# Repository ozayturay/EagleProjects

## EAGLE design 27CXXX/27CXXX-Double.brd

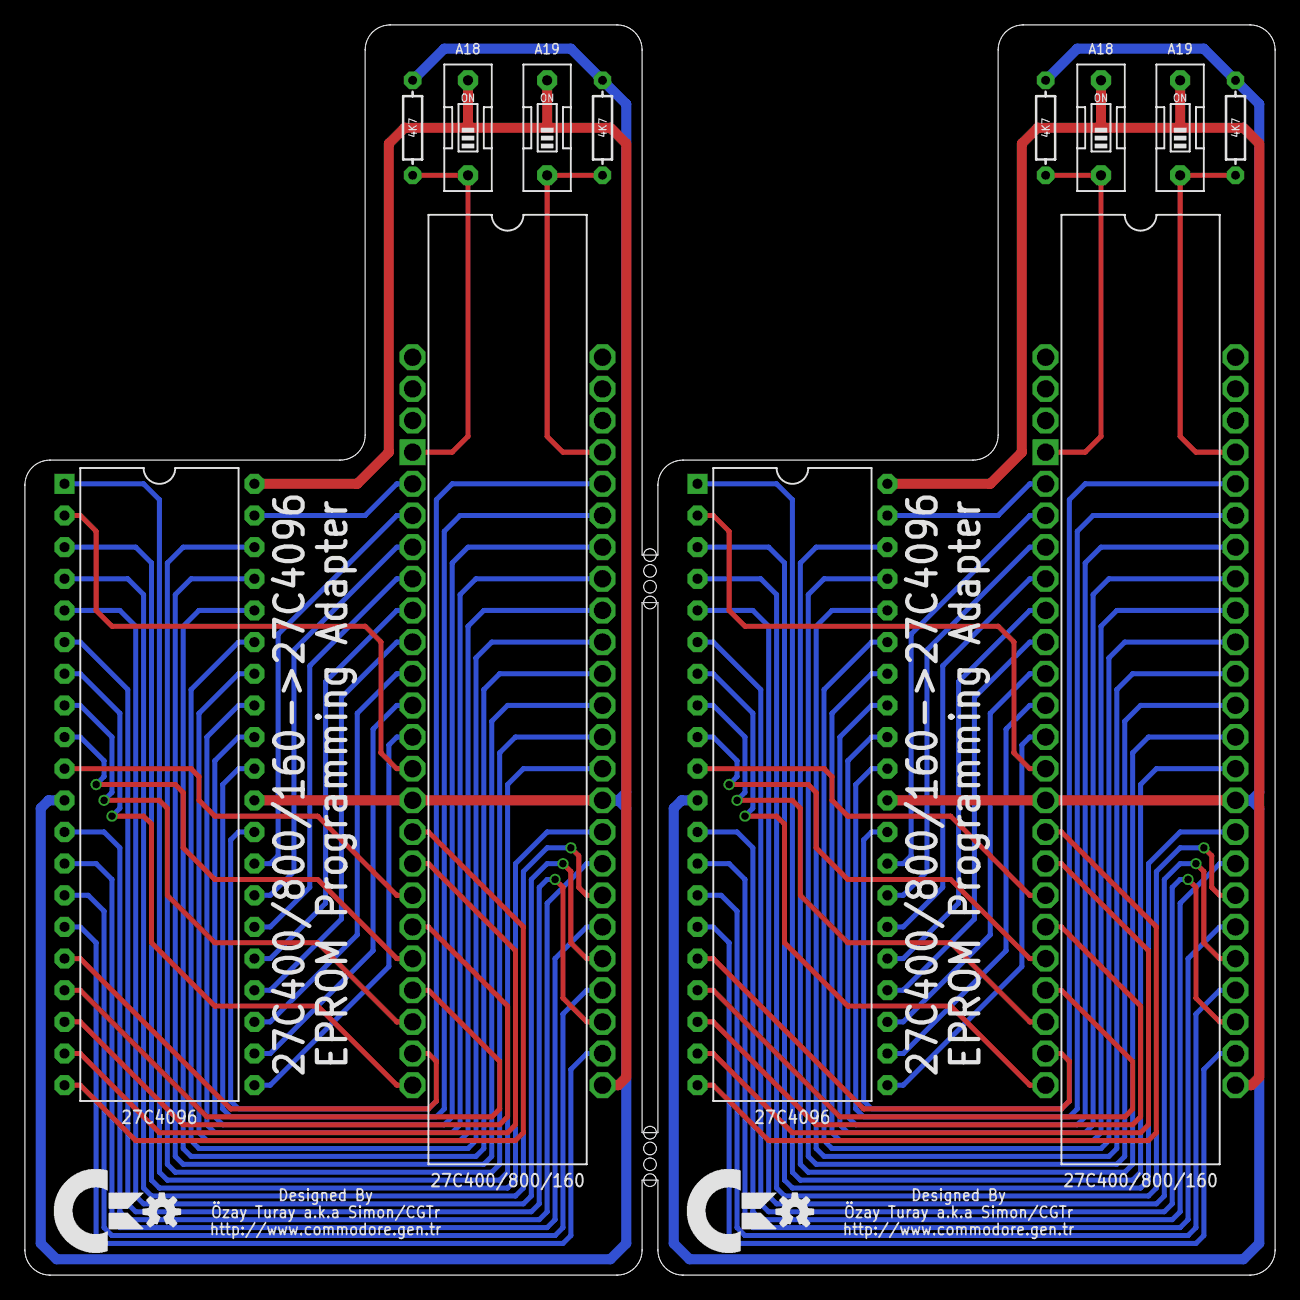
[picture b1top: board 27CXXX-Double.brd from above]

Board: 2 copper layers, 100.3 x 100.3 mm, 14 parts (0 on the bottom side), 82 nets.

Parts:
IC1, IC3: 27C4096; DIP40W
IC2, IC4: 27C400/800/160; ZIF42F
LOGO1, LOGO2: OSHW_LOGO_SMALL
R1, R2, R3, R4: 4K7; RESISTOR_0.3
SW1, SW3: A18; SWITCH_DIP_01
SW2, SW4: A19; SWITCH_DIP_01

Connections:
!CE: IC1.2, IC2.11
!CE1: IC3.2, IC4.11
!OE: IC1.20, IC2.13
!OE1: IC3.20, IC4.13
A0: IC1.21, IC2.10
A1: IC1.22, IC2.9
A2: IC1.23, IC2.8
A3: IC1.24, IC2.7
A4: IC1.25, IC2.6
A5: IC1.26, IC2.5
A6: IC1.27, IC2.4
A7: IC1.28, IC2.3
A8: IC1.29, IC2.41
A9: IC1.31, IC2.40
A10: IC1.32, IC2.39
A11: IC1.33, IC2.38
A12: IC1.34, IC2.37
A13: IC1.35, IC2.36
A14: IC1.36, IC2.35
A15: IC1.37, IC2.34
A16: IC1.38, IC2.33
A17: IC1.39, IC2.2
A18: IC2.1, R1.1, SW1.1
A19: IC2.42, R2.1, SW2.1
A20: IC3.21, IC4.10
A21: IC3.22, IC4.9
A22: IC3.23, IC4.8
A23: IC3.24, IC4.7
A24: IC3.25, IC4.6
A25: IC3.26, IC4.5
A26: IC3.27, IC4.4
A27: IC3.28, IC4.3
A28: IC3.29, IC4.41
A29: IC3.31, IC4.40
A30: IC3.32, IC4.39
A31: IC3.36, IC4.35
A32: IC3.33, IC4.38
A33: IC3.34, IC4.37
A34: IC3.37, IC4.34
A35: IC3.35, IC4.36
A36: IC3.38, IC4.33
A37: IC3.39, IC4.2
A38: IC4.1, R3.1, SW3.1
A39: IC4.42, R4.1, SW4.1
GND: IC1.11, IC1.30, IC2.12, IC2.31, R1.2, R2.2
GND1: IC3.11, IC3.30, IC4.12, IC4.31, R3.2, R4.2
Q0: IC1.19, IC2.14
Q1: IC1.18, IC2.16
Q2: IC1.17, IC2.18
Q3: IC1.16, IC2.20
Q4: IC1.15, IC2.23
Q5: IC1.14, IC2.25
Q6: IC1.13, IC2.27
Q7: IC1.12, IC2.29
Q8: IC1.10, IC2.15
Q9: IC1.9, IC2.17
Q10: IC1.8, IC2.19
Q11: IC1.7, IC2.21
Q12: IC1.6, IC2.24
Q13: IC1.5, IC2.26
Q14: IC1.4, IC2.28
Q15: IC1.3, IC2.30
Q16: IC3.19, IC4.14
Q17: IC3.18, IC4.16
Q18: IC3.17, IC4.18
Q19: IC3.16, IC4.20
Q20: IC3.15, IC4.23
Q21: IC3.14, IC4.25
Q22: IC3.13, IC4.27
Q23: IC3.12, IC4.29
Q24: IC3.10, IC4.15
Q25: IC3.9, IC4.17
Q26: IC3.8, IC4.19
Q27: IC3.7, IC4.21
Q28: IC3.6, IC4.24
Q29: IC3.5, IC4.26
Q30: IC3.4, IC4.28
Q31: IC3.3, IC4.30
VCC: IC1.40, IC2.22, SW1.2, SW2.2
VCC1: IC3.40, IC4.22, SW3.2, SW4.2
VPP: IC1.1, IC2.32
VPP1: IC3.1, IC4.32

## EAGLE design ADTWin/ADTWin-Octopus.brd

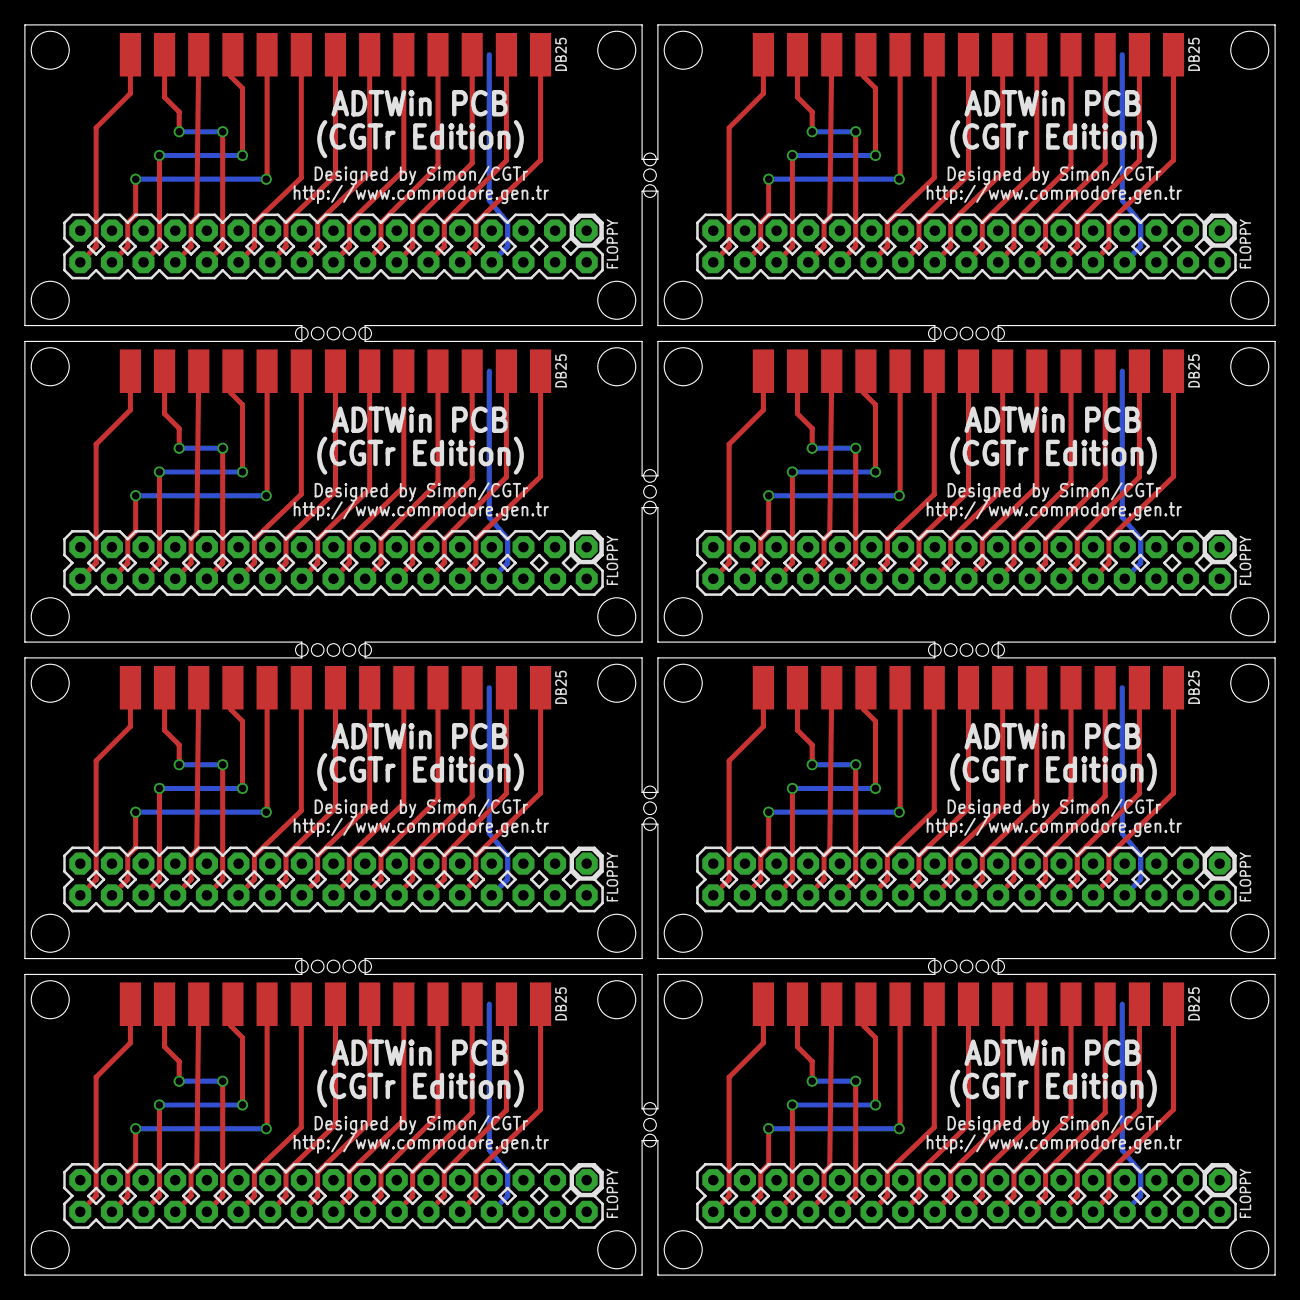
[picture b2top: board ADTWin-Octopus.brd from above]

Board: 2 copper layers, 100.3 x 100.3 mm, 16 parts (0 on the bottom side), 120 nets.

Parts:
JP1, JP2, JP3, JP4, JP5, JP6, JP7, JP8: FLOPPY
X1, X2, X3, X4, X5, X6, X7, X8: DB25; DSUB25-SMD

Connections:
DIR: JP1.18, X1.5
DIR1: JP2.18, X2.5
DIR2: JP3.18, X3.5
DIR3: JP4.18, X4.5
DIR4: JP5.18, X5.5
DIR5: JP6.18, X6.5
DIR6: JP7.18, X7.5
DIR7: JP8.18, X8.5
DRVSA: JP1.14, X1.3
DRVSA1: JP2.14, X2.3
DRVSA2: JP3.14, X3.3
DRVSA3: JP4.14, X4.3
DRVSA4: JP5.14, X5.3
DRVSA5: JP6.14, X6.3
DRVSA6: JP7.14, X7.3
DRVSA7: JP8.14, X8.3
DRVSB: JP1.12, X1.2
DRVSB1: JP2.12, X2.2
DRVSB2: JP3.12, X3.2
DRVSB3: JP4.12, X4.2
DRVSB4: JP5.12, X5.2
DRVSB5: JP6.12, X6.2
DRVSB6: JP7.12, X7.2
DRVSB7: JP8.12, X8.2
DSKCHG: JP1.34, X1.13
DSKCHG1: JP2.34, X2.13
DSKCHG2: JP3.34, X3.13
DSKCHG3: JP4.34, X4.13
DSKCHG4: JP5.34, X5.13
DSKCHG5: JP6.34, X6.13
DSKCHG6: JP7.34, X7.13
DSKCHG7: JP8.34, X8.13
GND: JP1.1, JP1.21, JP1.23, JP1.25, JP1.27, JP1.29, JP1.31, JP1.33, X1.18, X1.19, X1.20, X1.21, X1.22, X1.23, X1.24, X1.25
GND1: JP2.1, JP2.21, JP2.23, JP2.25, JP2.27, JP2.29, JP2.31, JP2.33, X2.18, X2.19, X2.20, X2.21, X2.22, X2.23, X2.24, X2.25
GND2: JP3.1, JP3.21, JP3.23, JP3.25, JP3.27, JP3.29, JP3.31, JP3.33, X3.18, X3.19, X3.20, X3.21, X3.22, X3.23, X3.24, X3.25
GND3: JP4.1, JP4.21, JP4.23, JP4.25, JP4.27, JP4.29, JP4.31, JP4.33, X4.18, X4.19, X4.20, X4.21, X4.22, X4.23, X4.24, X4.25
GND4: JP5.1, JP5.21, JP5.23, JP5.25, JP5.27, JP5.29, JP5.31, JP5.33, X5.18, X5.19, X5.20, X5.21, X5.22, X5.23, X5.24, X5.25
GND5: JP6.1, JP6.21, JP6.23, JP6.25, JP6.27, JP6.29, JP6.31, JP6.33, X6.18, X6.19, X6.20, X6.21, X6.22, X6.23, X6.24, X6.25
GND6: JP7.1, JP7.21, JP7.23, JP7.25, JP7.27, JP7.29, JP7.31, JP7.33, X7.18, X7.19, X7.20, X7.21, X7.22, X7.23, X7.24, X7.25
GND7: JP8.1, JP8.21, JP8.23, JP8.25, JP8.27, JP8.29, JP8.31, JP8.33, X8.18, X8.19, X8.20, X8.21, X8.22, X8.23, X8.24, X8.25
INDEX: JP1.8, X1.15
INDEX1: JP2.8, X2.15
INDEX2: JP3.8, X3.15
INDEX3: JP4.8, X4.15
INDEX4: JP5.8, X5.15
INDEX5: JP6.8, X6.15
INDEX6: JP7.8, X7.15
INDEX7: JP8.8, X8.15
MOTEA: JP1.10, X1.1
MOTEA1: JP2.10, X2.1
MOTEA2: JP3.10, X3.1
MOTEA3: JP4.10, X4.1
MOTEA4: JP5.10, X5.1
MOTEA5: JP6.10, X6.1
MOTEA6: JP7.10, X7.1
MOTEA7: JP8.10, X8.1
MOTEB: JP1.16, X1.4
MOTEB1: JP2.16, X2.4
MOTEB2: JP3.16, X3.4
MOTEB3: JP4.16, X4.4
MOTEB4: JP5.16, X5.4
MOTEB5: JP6.16, X6.4
MOTEB6: JP7.16, X7.4
MOTEB7: JP8.16, X8.4
RDATA: JP1.30, X1.10
RDATA1: JP2.30, X2.10
RDATA2: JP3.30, X3.10
RDATA3: JP4.30, X4.10
RDATA4: JP5.30, X5.10
RDATA5: JP6.30, X6.10
RDATA6: JP7.30, X7.10
RDATA7: JP8.30, X8.10
SIDE1: JP1.32, X1.9
SIDE2: JP2.32, X2.9
SIDE3: JP3.32, X3.9
SIDE4: JP4.32, X4.9
SIDE5: JP5.32, X5.9
SIDE6: JP6.32, X6.9
SIDE7: JP7.32, X7.9
SIDE8: JP8.32, X8.9
STEP: JP1.20, X1.6
STEP1: JP2.20, X2.6
STEP2: JP3.20, X3.6
STEP3: JP4.20, X4.6
STEP4: JP5.20, X5.6
STEP5: JP6.20, X6.6
STEP6: JP7.20, X7.6
STEP7: JP8.20, X8.6
TRK00: JP1.26, X1.12
TRK01: JP2.26, X2.12
TRK02: JP3.26, X3.12
TRK03: JP4.26, X4.12
TRK04: JP5.26, X5.12
TRK05: JP6.26, X6.12
TRK06: JP7.26, X7.12
TRK07: JP8.26, X8.12
WDATA: JP1.22, X1.7
WDATA1: JP2.22, X2.7
WDATA2: JP3.22, X3.7
WDATA3: JP4.22, X4.7
WDATA4: JP5.22, X5.7
WDATA5: JP6.22, X6.7
WDATA6: JP7.22, X7.7
WDATA7: JP8.22, X8.7
WGATE: JP1.24, X1.8
WGATE1: JP2.24, X2.8
WGATE2: JP3.24, X3.8
WGATE3: JP4.24, X4.8
WGATE4: JP5.24, X5.8
WGATE5: JP6.24, X6.8
WGATE6: JP7.24, X7.8
WGATE7: JP8.24, X8.8
WPROT: JP1.28, X1.11
WPROT1: JP2.28, X2.11
WPROT2: JP3.28, X3.11
WPROT3: JP4.28, X4.11
WPROT4: JP5.28, X5.11
WPROT5: JP6.28, X6.11
WPROT6: JP7.28, X7.11
WPROT7: JP8.28, X8.11

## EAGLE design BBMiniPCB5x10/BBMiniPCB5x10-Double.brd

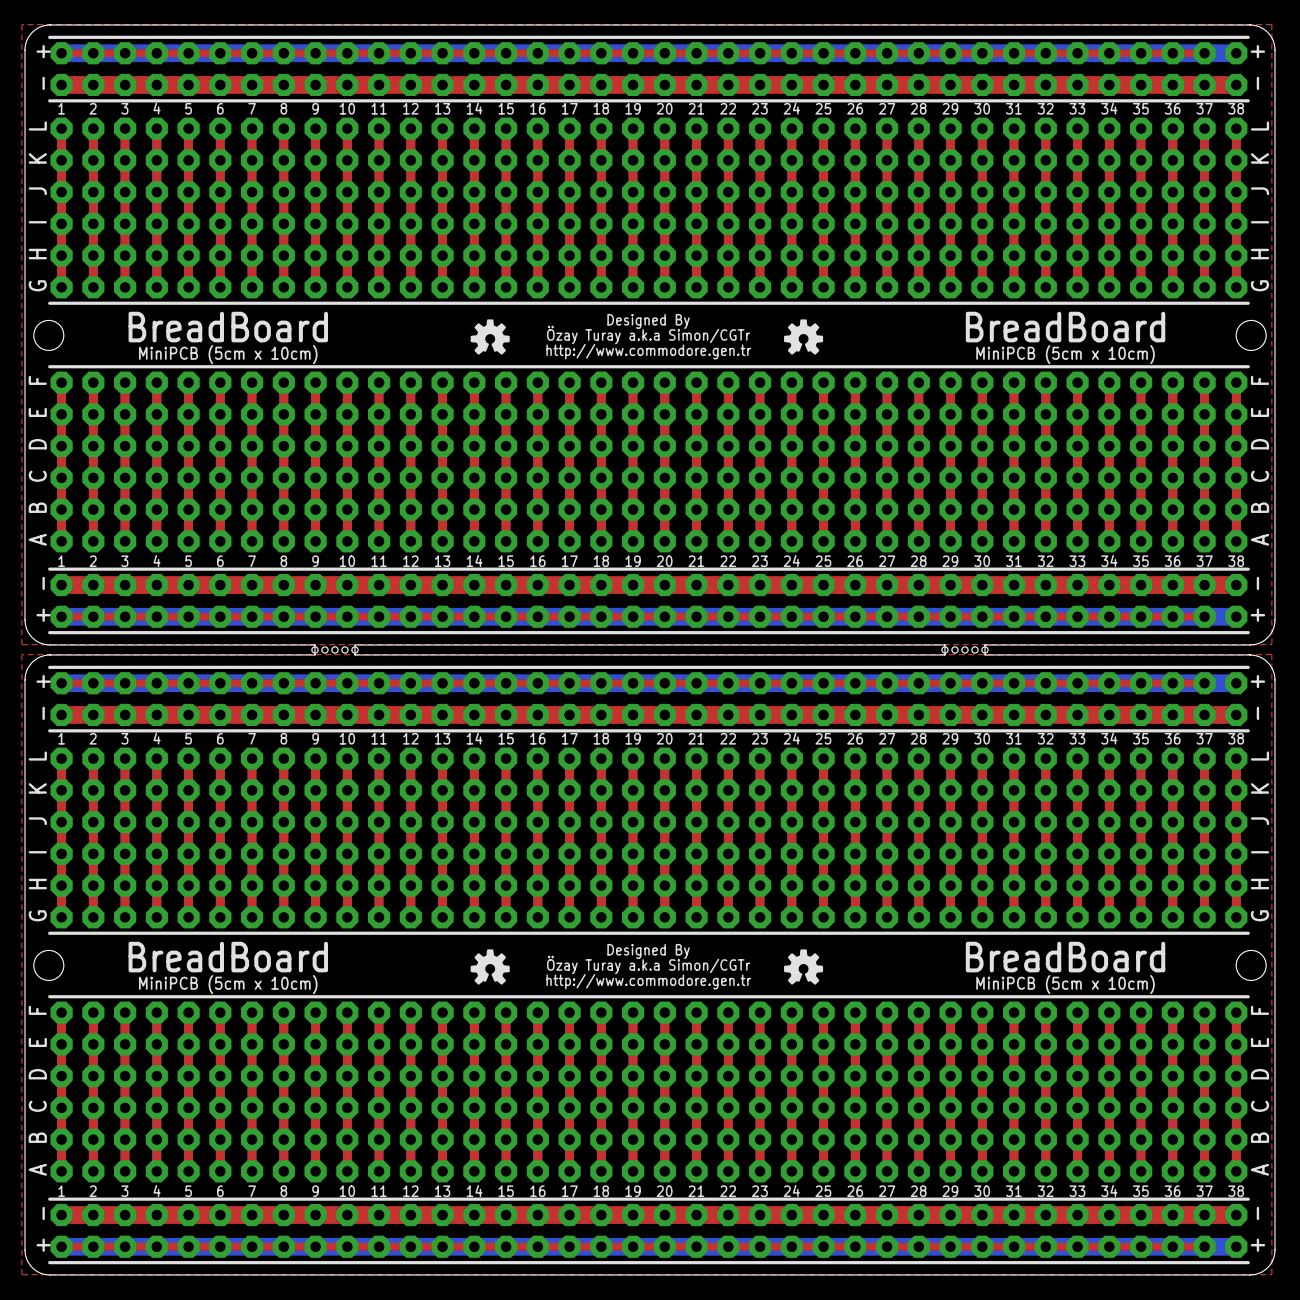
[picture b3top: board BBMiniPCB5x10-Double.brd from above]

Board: 2 copper layers, 100.0 x 100.0 mm, 164 parts (0 on the bottom side), 156 nets.

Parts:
B1, B39: 1; HDR_1X06_NOSILK
B2, B40: 2; HDR_1X06_NOSILK
B3, B41: 3; HDR_1X06_NOSILK
B4, B42: 4; HDR_1X06_NOSILK
B5, B43: 5; HDR_1X06_NOSILK
B6, B44: 6; HDR_1X06_NOSILK
B7, B45: 7; HDR_1X06_NOSILK
B8, B46: 8; HDR_1X06_NOSILK
B9, B47: 9; HDR_1X06_NOSILK
B10, B48: 10; HDR_1X06_NOSILK
B11, B49: 11; HDR_1X06_NOSILK
B12, B50: 12; HDR_1X06_NOSILK
B13, B51: 13; HDR_1X06_NOSILK
B14, B52: 14; HDR_1X06_NOSILK
B15, B53: 15; HDR_1X06_NOSILK
B16, B54: 16; HDR_1X06_NOSILK
B17, B55: 17; HDR_1X06_NOSILK
B18, B56: 18; HDR_1X06_NOSILK
B19, B57: 19; HDR_1X06_NOSILK
B20, B58: 20; HDR_1X06_NOSILK
B21, B59: 21; HDR_1X06_NOSILK
B22, B60: 22; HDR_1X06_NOSILK
B23, B61: 23; HDR_1X06_NOSILK
B24, B62: 24; HDR_1X06_NOSILK
B25, B63: 25; HDR_1X06_NOSILK
B26, B64: 26; HDR_1X06_NOSILK
B27, B65: 27; HDR_1X06_NOSILK
B28, B66: 28; HDR_1X06_NOSILK
B29, B67: 29; HDR_1X06_NOSILK
B30, B68: 30; HDR_1X06_NOSILK
B31, B69: 31; HDR_1X06_NOSILK
B32, B70: 32; HDR_1X06_NOSILK
B33, B71: 33; HDR_1X06_NOSILK
B34, B72: 34; HDR_1X06_NOSILK
B35, B73: 35; HDR_1X06_NOSILK
B36, B74: 36; HDR_1X06_NOSILK
B37, B75: 37; HDR_1X06_NOSILK
B38, B76: 38; HDR_1X06_NOSILK
G1, G2, G3, G4: -; HDR_1X38_NOSILK
LOGO1, LOGO2, LOGO3, LOGO4: OSHW_LOGO_SMALL
P1, P2, P3, P4: +; HDR_1X38_NOSILK
T1, T39: 1; HDR_1X06_NOSILK
T2, T40: 2; HDR_1X06_NOSILK
T3, T41: 3; HDR_1X06_NOSILK
T4, T42: 4; HDR_1X06_NOSILK
T5, T43: 5; HDR_1X06_NOSILK
T6, T44: 6; HDR_1X06_NOSILK
T7, T45: 7; HDR_1X06_NOSILK
T8, T46: 8; HDR_1X06_NOSILK
T9, T47: 9; HDR_1X06_NOSILK
T10, T48: 10; HDR_1X06_NOSILK
T11, T49: 11; HDR_1X06_NOSILK
T12, T50: 12; HDR_1X06_NOSILK
T13, T51: 13; HDR_1X06_NOSILK
T14, T52: 14; HDR_1X06_NOSILK
T15, T53: 15; HDR_1X06_NOSILK
T16, T54: 16; HDR_1X06_NOSILK
T17, T55: 17; HDR_1X06_NOSILK
T18, T56: 18; HDR_1X06_NOSILK
T19, T57: 19; HDR_1X06_NOSILK
T20, T58: 20; HDR_1X06_NOSILK
T21, T59: 21; HDR_1X06_NOSILK
T22, T60: 22; HDR_1X06_NOSILK
T23, T61: 23; HDR_1X06_NOSILK
T24, T62: 24; HDR_1X06_NOSILK
T25, T63: 25; HDR_1X06_NOSILK
T26, T64: 26; HDR_1X06_NOSILK
T27, T65: 27; HDR_1X06_NOSILK
T28, T66: 28; HDR_1X06_NOSILK
T29, T67: 29; HDR_1X06_NOSILK
T30, T68: 30; HDR_1X06_NOSILK
T31, T69: 31; HDR_1X06_NOSILK
T32, T70: 32; HDR_1X06_NOSILK
T33, T71: 33; HDR_1X06_NOSILK
T34, T72: 34; HDR_1X06_NOSILK
T35, T73: 35; HDR_1X06_NOSILK
T36, T74: 36; HDR_1X06_NOSILK
T37, T75: 37; HDR_1X06_NOSILK
T38, T76: 38; HDR_1X06_NOSILK

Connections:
B1: B1.1, B1.2, B1.3, B1.4, B1.5, B1.6
B2: B2.1, B2.2, B2.3, B2.4, B2.5, B2.6
B3: B3.1, B3.2, B3.3, B3.4, B3.5, B3.6
B4: B4.1, B4.2, B4.3, B4.4, B4.5, B4.6
B5: B5.1, B5.2, B5.3, B5.4, B5.5, B5.6
B6: B6.1, B6.2, B6.3, B6.4, B6.5, B6.6
B7: B7.1, B7.2, B7.3, B7.4, B7.5, B7.6
B8: B8.1, B8.2, B8.3, B8.4, B8.5, B8.6
B9: B9.1, B9.2, B9.3, B9.4, B9.5, B9.6
B10: B10.1, B10.2, B10.3, B10.4, B10.5, B10.6
B11: B11.1, B11.2, B11.3, B11.4, B11.5, B11.6
B12: B12.1, B12.2, B12.3, B12.4, B12.5, B12.6
B13: B13.1, B13.2, B13.3, B13.4, B13.5, B13.6
B14: B14.1, B14.2, B14.3, B14.4, B14.5, B14.6
B15: B15.1, B15.2, B15.3, B15.4, B15.5, B15.6
B16: B16.1, B16.2, B16.3, B16.4, B16.5, B16.6
B17: B17.1, B17.2, B17.3, B17.4, B17.5, B17.6
B18: B18.1, B18.2, B18.3, B18.4, B18.5, B18.6
B19: B19.1, B19.2, B19.3, B19.4, B19.5, B19.6
B20: B20.1, B20.2, B20.3, B20.4, B20.5, B20.6
B21: B21.1, B21.2, B21.3, B21.4, B21.5, B21.6
B22: B22.1, B22.2, B22.3, B22.4, B22.5, B22.6
B23: B23.1, B23.2, B23.3, B23.4, B23.5, B23.6
B24: B24.1, B24.2, B24.3, B24.4, B24.5, B24.6
B25: B25.1, B25.2, B25.3, B25.4, B25.5, B25.6
B26: B26.1, B26.2, B26.3, B26.4, B26.5, B26.6
B27: B27.1, B27.2, B27.3, B27.4, B27.5, B27.6
B28: B28.1, B28.2, B28.3, B28.4, B28.5, B28.6
B29: B29.1, B29.2, B29.3, B29.4, B29.5, B29.6
B30: B30.1, B30.2, B30.3, B30.4, B30.5, B30.6
B31: B31.1, B31.2, B31.3, B31.4, B31.5, B31.6
B32: B32.1, B32.2, B32.3, B32.4, B32.5, B32.6
B33: B33.1, B33.2, B33.3, B33.4, B33.5, B33.6
B34: B34.1, B34.2, B34.3, B34.4, B34.5, B34.6
B35: B35.1, B35.2, B35.3, B35.4, B35.5, B35.6
B36: B36.1, B36.2, B36.3, B36.4, B36.5, B36.6
B37: B37.1, B37.2, B37.3, B37.4, B37.5, B37.6
B38: B38.1, B38.2, B38.3, B38.4, B38.5, B38.6
B39: B39.1, B39.2, B39.3, B39.4, B39.5, B39.6
B40: B40.1, B40.2, B40.3, B40.4, B40.5, B40.6
B41: B41.1, B41.2, B41.3, B41.4, B41.5, B41.6
B42: B42.1, B42.2, B42.3, B42.4, B42.5, B42.6
B43: B43.1, B43.2, B43.3, B43.4, B43.5, B43.6
B44: B44.1, B44.2, B44.3, B44.4, B44.5, B44.6
B45: B45.1, B45.2, B45.3, B45.4, B45.5, B45.6
B46: B46.1, B46.2, B46.3, B46.4, B46.5, B46.6
B47: B47.1, B47.2, B47.3, B47.4, B47.5, B47.6
B48: B48.1, B48.2, B48.3, B48.4, B48.5, B48.6
B49: B49.1, B49.2, B49.3, B49.4, B49.5, B49.6
B50: B50.1, B50.2, B50.3, B50.4, B50.5, B50.6
B51: B51.1, B51.2, B51.3, B51.4, B51.5, B51.6
B52: B52.1, B52.2, B52.3, B52.4, B52.5, B52.6
B53: B53.1, B53.2, B53.3, B53.4, B53.5, B53.6
B54: B54.1, B54.2, B54.3, B54.4, B54.5, B54.6
B55: B55.1, B55.2, B55.3, B55.4, B55.5, B55.6
B56: B56.1, B56.2, B56.3, B56.4, B56.5, B56.6
B57: B57.1, B57.2, B57.3, B57.4, B57.5, B57.6
B58: B58.1, B58.2, B58.3, B58.4, B58.5, B58.6
B59: B59.1, B59.2, B59.3, B59.4, B59.5, B59.6
B60: B60.1, B60.2, B60.3, B60.4, B60.5, B60.6
B61: B61.1, B61.2, B61.3, B61.4, B61.5, B61.6
B62: B62.1, B62.2, B62.3, B62.4, B62.5, B62.6
B63: B63.1, B63.2, B63.3, B63.4, B63.5, B63.6
B64: B64.1, B64.2, B64.3, B64.4, B64.5, B64.6
B65: B65.1, B65.2, B65.3, B65.4, B65.5, B65.6
B66: B66.1, B66.2, B66.3, B66.4, B66.5, B66.6
B67: B67.1, B67.2, B67.3, B67.4, B67.5, B67.6
B68: B68.1, B68.2, B68.3, B68.4, B68.5, B68.6
B69: B69.1, B69.2, B69.3, B69.4, B69.5, B69.6
B70: B70.1, B70.2, B70.3, B70.4, B70.5, B70.6
B71: B71.1, B71.2, B71.3, B71.4, B71.5, B71.6
B72: B72.1, B72.2, B72.3, B72.4, B72.5, B72.6
B73: B73.1, B73.2, B73.3, B73.4, B73.5, B73.6
B74: B74.1, B74.2, B74.3, B74.4, B74.5, B74.6
B75: B75.1, B75.2, B75.3, B75.4, B75.5, B75.6
B76: B76.1, B76.2, B76.3, B76.4, B76.5, B76.6
GND: G1.1, G1.2, G1.3, G1.4, G1.5, G1.6, G1.7, G1.8, G1.9, G1.10, G1.11, G1.12, G1.13, G1.14, G1.15, G1.16, G1.17, G1.18, G1.19, G1.20, G1.21, G1.22, G1.23, G1.24, G1.25, G1.26, G1.27, G1.28, G1.29, G1.30, G1.31, G1.32, G1.33, G1.34, G1.35, G1.36, G1.37, G1.38, G2.1, G2.2, G2.3, G2.4, G2.5, G2.6, G2.7, G2.8, G2.9, G2.10, G2.11, G2.12, G2.13, G2.14, G2.15, G2.16, G2.17, G2.18, G2.19, G2.20, G2.21, G2.22, G2.23, G2.24, G2.25, G2.26, G2.27, G2.28, G2.29, G2.30, G2.31, G2.32, G2.33, G2.34, G2.35, G2.36, G2.37, G2.38
GND1: G3.1, G3.2, G3.3, G3.4, G3.5, G3.6, G3.7, G3.8, G3.9, G3.10, G3.11, G3.12, G3.13, G3.14, G3.15, G3.16, G3.17, G3.18, G3.19, G3.20, G3.21, G3.22, G3.23, G3.24, G3.25, G3.26, G3.27, G3.28, G3.29, G3.30, G3.31, G3.32, G3.33, G3.34, G3.35, G3.36, G3.37, G3.38, G4.1, G4.2, G4.3, G4.4, G4.5, G4.6, G4.7, G4.8, G4.9, G4.10, G4.11, G4.12, G4.13, G4.14, G4.15, G4.16, G4.17, G4.18, G4.19, G4.20, G4.21, G4.22, G4.23, G4.24, G4.25, G4.26, G4.27, G4.28, G4.29, G4.30, G4.31, G4.32, G4.33, G4.34, G4.35, G4.36, G4.37, G4.38
T1: T1.1, T1.2, T1.3, T1.4, T1.5, T1.6
T2: T2.1, T2.2, T2.3, T2.4, T2.5, T2.6
T3: T3.1, T3.2, T3.3, T3.4, T3.5, T3.6
T4: T4.1, T4.2, T4.3, T4.4, T4.5, T4.6
T5: T5.1, T5.2, T5.3, T5.4, T5.5, T5.6
T6: T6.1, T6.2, T6.3, T6.4, T6.5, T6.6
T7: T7.1, T7.2, T7.3, T7.4, T7.5, T7.6
T8: T8.1, T8.2, T8.3, T8.4, T8.5, T8.6
T9: T9.1, T9.2, T9.3, T9.4, T9.5, T9.6
T10: T10.1, T10.2, T10.3, T10.4, T10.5, T10.6
T11: T11.1, T11.2, T11.3, T11.4, T11.5, T11.6
T12: T12.1, T12.2, T12.3, T12.4, T12.5, T12.6
T13: T13.1, T13.2, T13.3, T13.4, T13.5, T13.6
T14: T14.1, T14.2, T14.3, T14.4, T14.5, T14.6
T15: T15.1, T15.2, T15.3, T15.4, T15.5, T15.6
T16: T16.1, T16.2, T16.3, T16.4, T16.5, T16.6
T17: T17.1, T17.2, T17.3, T17.4, T17.5, T17.6
T18: T18.1, T18.2, T18.3, T18.4, T18.5, T18.6
T19: T19.1, T19.2, T19.3, T19.4, T19.5, T19.6
T20: T20.1, T20.2, T20.3, T20.4, T20.5, T20.6
T21: T21.1, T21.2, T21.3, T21.4, T21.5, T21.6
T22: T22.1, T22.2, T22.3, T22.4, T22.5, T22.6
T23: T23.1, T23.2, T23.3, T23.4, T23.5, T23.6
T24: T24.1, T24.2, T24.3, T24.4, T24.5, T24.6
T25: T25.1, T25.2, T25.3, T25.4, T25.5, T25.6
T26: T26.1, T26.2, T26.3, T26.4, T26.5, T26.6
T27: T27.1, T27.2, T27.3, T27.4, T27.5, T27.6
T28: T28.1, T28.2, T28.3, T28.4, T28.5, T28.6
T29: T29.1, T29.2, T29.3, T29.4, T29.5, T29.6
T30: T30.1, T30.2, T30.3, T30.4, T30.5, T30.6
T31: T31.1, T31.2, T31.3, T31.4, T31.5, T31.6
T32: T32.1, T32.2, T32.3, T32.4, T32.5, T32.6
T33: T33.1, T33.2, T33.3, T33.4, T33.5, T33.6
T34: T34.1, T34.2, T34.3, T34.4, T34.5, T34.6
T35: T35.1, T35.2, T35.3, T35.4, T35.5, T35.6
T36: T36.1, T36.2, T36.3, T36.4, T36.5, T36.6
T37: T37.1, T37.2, T37.3, T37.4, T37.5, T37.6
T38: T38.1, T38.2, T38.3, T38.4, T38.5, T38.6
T39: T39.1, T39.2, T39.3, T39.4, T39.5, T39.6
T40: T40.1, T40.2, T40.3, T40.4, T40.5, T40.6
T41: T41.1, T41.2, T41.3, T41.4, T41.5, T41.6
T42: T42.1, T42.2, T42.3, T42.4, T42.5, T42.6
T43: T43.1, T43.2, T43.3, T43.4, T43.5, T43.6
T44: T44.1, T44.2, T44.3, T44.4, T44.5, T44.6
T45: T45.1, T45.2, T45.3, T45.4, T45.5, T45.6
T46: T46.1, T46.2, T46.3, T46.4, T46.5, T46.6
T47: T47.1, T47.2, T47.3, T47.4, T47.5, T47.6
T48: T48.1, T48.2, T48.3, T48.4, T48.5, T48.6
T49: T49.1, T49.2, T49.3, T49.4, T49.5, T49.6
T50: T50.1, T50.2, T50.3, T50.4, T50.5, T50.6
T51: T51.1, T51.2, T51.3, T51.4, T51.5, T51.6
T52: T52.1, T52.2, T52.3, T52.4, T52.5, T52.6
T53: T53.1, T53.2, T53.3, T53.4, T53.5, T53.6
T54: T54.1, T54.2, T54.3, T54.4, T54.5, T54.6
T55: T55.1, T55.2, T55.3, T55.4, T55.5, T55.6
T56: T56.1, T56.2, T56.3, T56.4, T56.5, T56.6
T57: T57.1, T57.2, T57.3, T57.4, T57.5, T57.6
T58: T58.1, T58.2, T58.3, T58.4, T58.5, T58.6
T59: T59.1, T59.2, T59.3, T59.4, T59.5, T59.6
T60: T60.1, T60.2, T60.3, T60.4, T60.5, T60.6
T61: T61.1, T61.2, T61.3, T61.4, T61.5, T61.6
T62: T62.1, T62.2, T62.3, T62.4, T62.5, T62.6
T63: T63.1, T63.2, T63.3, T63.4, T63.5, T63.6
T64: T64.1, T64.2, T64.3, T64.4, T64.5, T64.6
T65: T65.1, T65.2, T65.3, T65.4, T65.5, T65.6
T66: T66.1, T66.2, T66.3, T66.4, T66.5, T66.6
T67: T67.1, T67.2, T67.3, T67.4, T67.5, T67.6
T68: T68.1, T68.2, T68.3, T68.4, T68.5, T68.6
T69: T69.1, T69.2, T69.3, T69.4, T69.5, T69.6
T70: T70.1, T70.2, T70.3, T70.4, T70.5, T70.6
T71: T71.1, T71.2, T71.3, T71.4, T71.5, T71.6
T72: T72.1, T72.2, T72.3, T72.4, T72.5, T72.6
T73: T73.1, T73.2, T73.3, T73.4, T73.5, T73.6
T74: T74.1, T74.2, T74.3, T74.4, T74.5, T74.6
T75: T75.1, T75.2, T75.3, T75.4, T75.5, T75.6
T76: T76.1, T76.2, T76.3, T76.4, T76.5, T76.6
VCC: P1.1, P1.2, P1.3, P1.4, P1.5, P1.6, P1.7, P1.8, P1.9, P1.10, P1.11, P1.12, P1.13, P1.14, P1.15, P1.16, P1.17, P1.18, P1.19, P1.20, P1.21, P1.22, P1.23, P1.24, P1.25, P1.26, P1.27, P1.28, P1.29, P1.30, P1.31, P1.32, P1.33, P1.34, P1.35, P1.36, P1.37, P1.38, P2.1, P2.2, P2.3, P2.4, P2.5, P2.6, P2.7, P2.8, P2.9, P2.10, P2.11, P2.12, P2.13, P2.14, P2.15, P2.16, P2.17, P2.18, P2.19, P2.20, P2.21, P2.22, P2.23, P2.24, P2.25, P2.26, P2.27, P2.28, P2.29, P2.30, P2.31, P2.32, P2.33, P2.34, P2.35, P2.36, P2.37, P2.38
VCC1: P3.1, P3.2, P3.3, P3.4, P3.5, P3.6, P3.7, P3.8, P3.9, P3.10, P3.11, P3.12, P3.13, P3.14, P3.15, P3.16, P3.17, P3.18, P3.19, P3.20, P3.21, P3.22, P3.23, P3.24, P3.25, P3.26, P3.27, P3.28, P3.29, P3.30, P3.31, P3.32, P3.33, P3.34, P3.35, P3.36, P3.37, P3.38, P4.1, P4.2, P4.3, P4.4, P4.5, P4.6, P4.7, P4.8, P4.9, P4.10, P4.11, P4.12, P4.13, P4.14, P4.15, P4.16, P4.17, P4.18, P4.19, P4.20, P4.21, P4.22, P4.23, P4.24, P4.25, P4.26, P4.27, P4.28, P4.29, P4.30, P4.31, P4.32, P4.33, P4.34, P4.35, P4.36, P4.37, P4.38

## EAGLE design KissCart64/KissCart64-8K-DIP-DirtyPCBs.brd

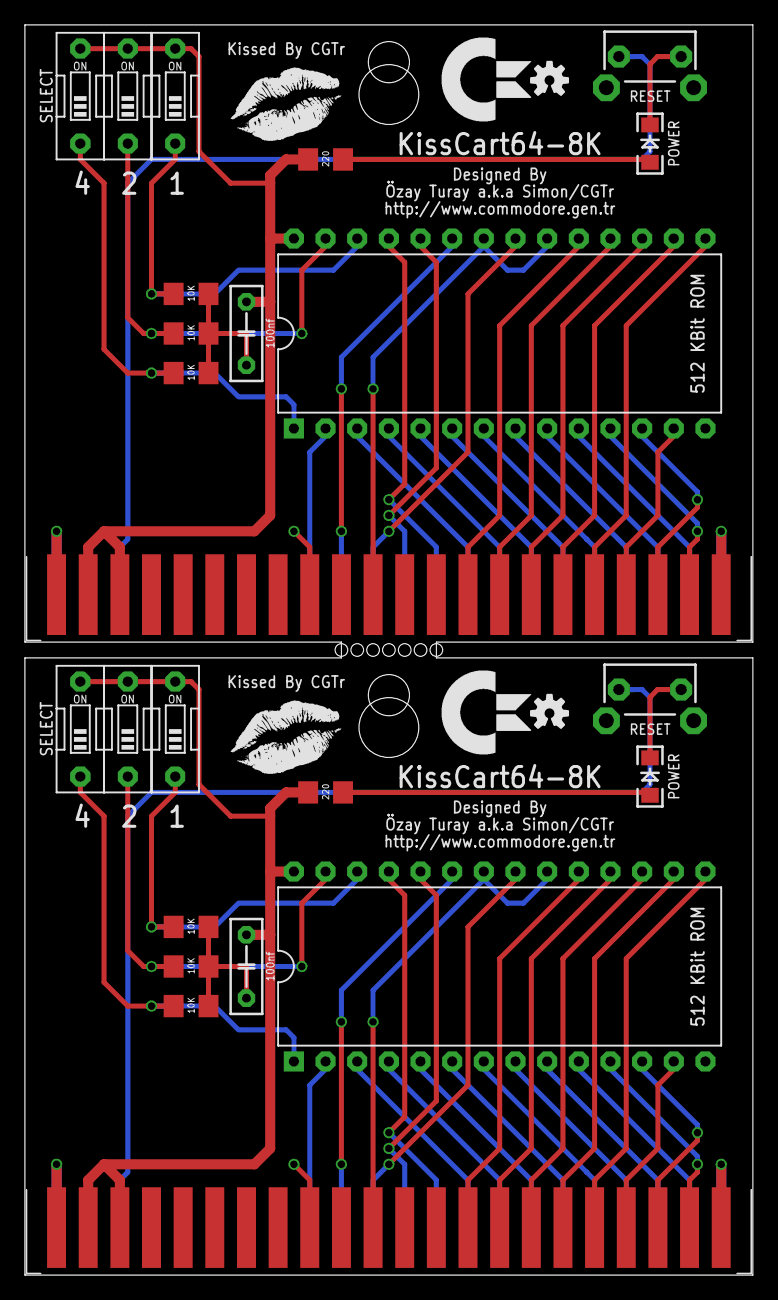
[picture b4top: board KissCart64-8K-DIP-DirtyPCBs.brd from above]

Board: 2 copper layers, 58.4 x 100.3 mm, 26 parts (0 on the bottom side), 58 nets.

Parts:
C1, C2: 100nf; CAPACITOR_CERAMIC_0.2
CONN1, CONN2: C64 EXPANSION; C64_CARTRIDGE
IC1, IC2: 512 KBit ROM; DIP28W
LED0, LED1: POWER; LED_1206
LOGO1, LOGO2: OSHW_LOGO_SMALL
R0, R1: 220; RESISTOR_SMT_1206
R2, R3, R4, R13, R14, R15: 10K; RESISTOR_SMT_1206
SW0, SW3: RESET; SWITCH_THT_SIDE
SW1, SW5: 1; SWITCH_DIP_01
SW2, SW6: 2; SWITCH_DIP_01
SW4, SW7: 4; SWITCH_DIP_01

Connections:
A0: CONN1.Y, IC1.10
A1: CONN1.X, IC1.9
A2: CONN1.W, IC1.8
A3: CONN1.V, IC1.7
A4: CONN1.U, IC1.6
A5: CONN1.T, IC1.5
A6: CONN1.S, IC1.4
A7: CONN1.R, IC1.3
A8: CONN1.P, IC1.25
A9: CONN1.N, IC1.24
A10: CONN1.M, IC1.21
A11: CONN1.L, IC1.23
A12: CONN1.K, IC1.2
A13: IC1.26, R13.1, SW1.1
A14: IC1.27, R14.1, SW2.1
A15: IC1.1, R15.1, SW4.1
A16: CONN2.Y, IC2.10
A17: CONN2.X, IC2.9
A18: CONN2.W, IC2.8
A19: CONN2.V, IC2.7
A20: CONN2.U, IC2.6
A21: CONN2.T, IC2.5
A22: CONN2.S, IC2.4
A23: CONN2.R, IC2.3
A24: CONN2.P, IC2.25
A25: CONN2.N, IC2.24
A26: CONN2.M, IC2.21
A27: CONN2.L, IC2.23
A28: CONN2.K, IC2.2
A29: IC2.1, R4.1, SW7.1
A30: IC2.27, R3.1, SW6.1
A31: IC2.26, R2.1, SW5.1
D0: CONN1.21, IC1.11
D1: CONN1.20, IC1.12
D2: CONN1.19, IC1.13
D3: CONN1.18, IC1.15
D4: CONN1.17, IC1.16
D5: CONN1.16, IC1.17
D6: CONN1.15, IC1.18
D7: CONN1.14, IC1.19
D8: CONN2.21, IC2.11
D9: CONN2.20, IC2.12
D10: CONN2.19, IC2.13
D11: CONN2.18, IC2.15
D12: CONN2.17, IC2.16
D13: CONN2.16, IC2.17
D14: CONN2.15, IC2.18
D15: CONN2.14, IC2.19
GND: C1.1, CONN1.1, CONN1.9, CONN1.22, CONN1.A, CONN1.Z, IC1.14, LED0.C, R13.2, R14.2, R15.2, SW0.1
GND1: C2.1, CONN2.1, CONN2.9, CONN2.22, CONN2.A, CONN2.Z, IC2.14, LED1.C, R2.2, R3.2, R4.2, SW3.1
LED0_1: LED0.A, R0.2
LED0_2: LED1.A, R1.2
RESET: CONN1.C, SW0.2
RESET1: CONN2.C, SW3.2
ROML: CONN1.11, IC1.20, IC1.22
ROML1: CONN2.11, IC2.20, IC2.22
VCC: C1.2, CONN1.2, CONN1.3, IC1.28, R0.1, SW1.2, SW2.2, SW4.2
VCC1: C2.2, CONN2.2, CONN2.3, IC2.28, R1.1, SW5.2, SW6.2, SW7.2
